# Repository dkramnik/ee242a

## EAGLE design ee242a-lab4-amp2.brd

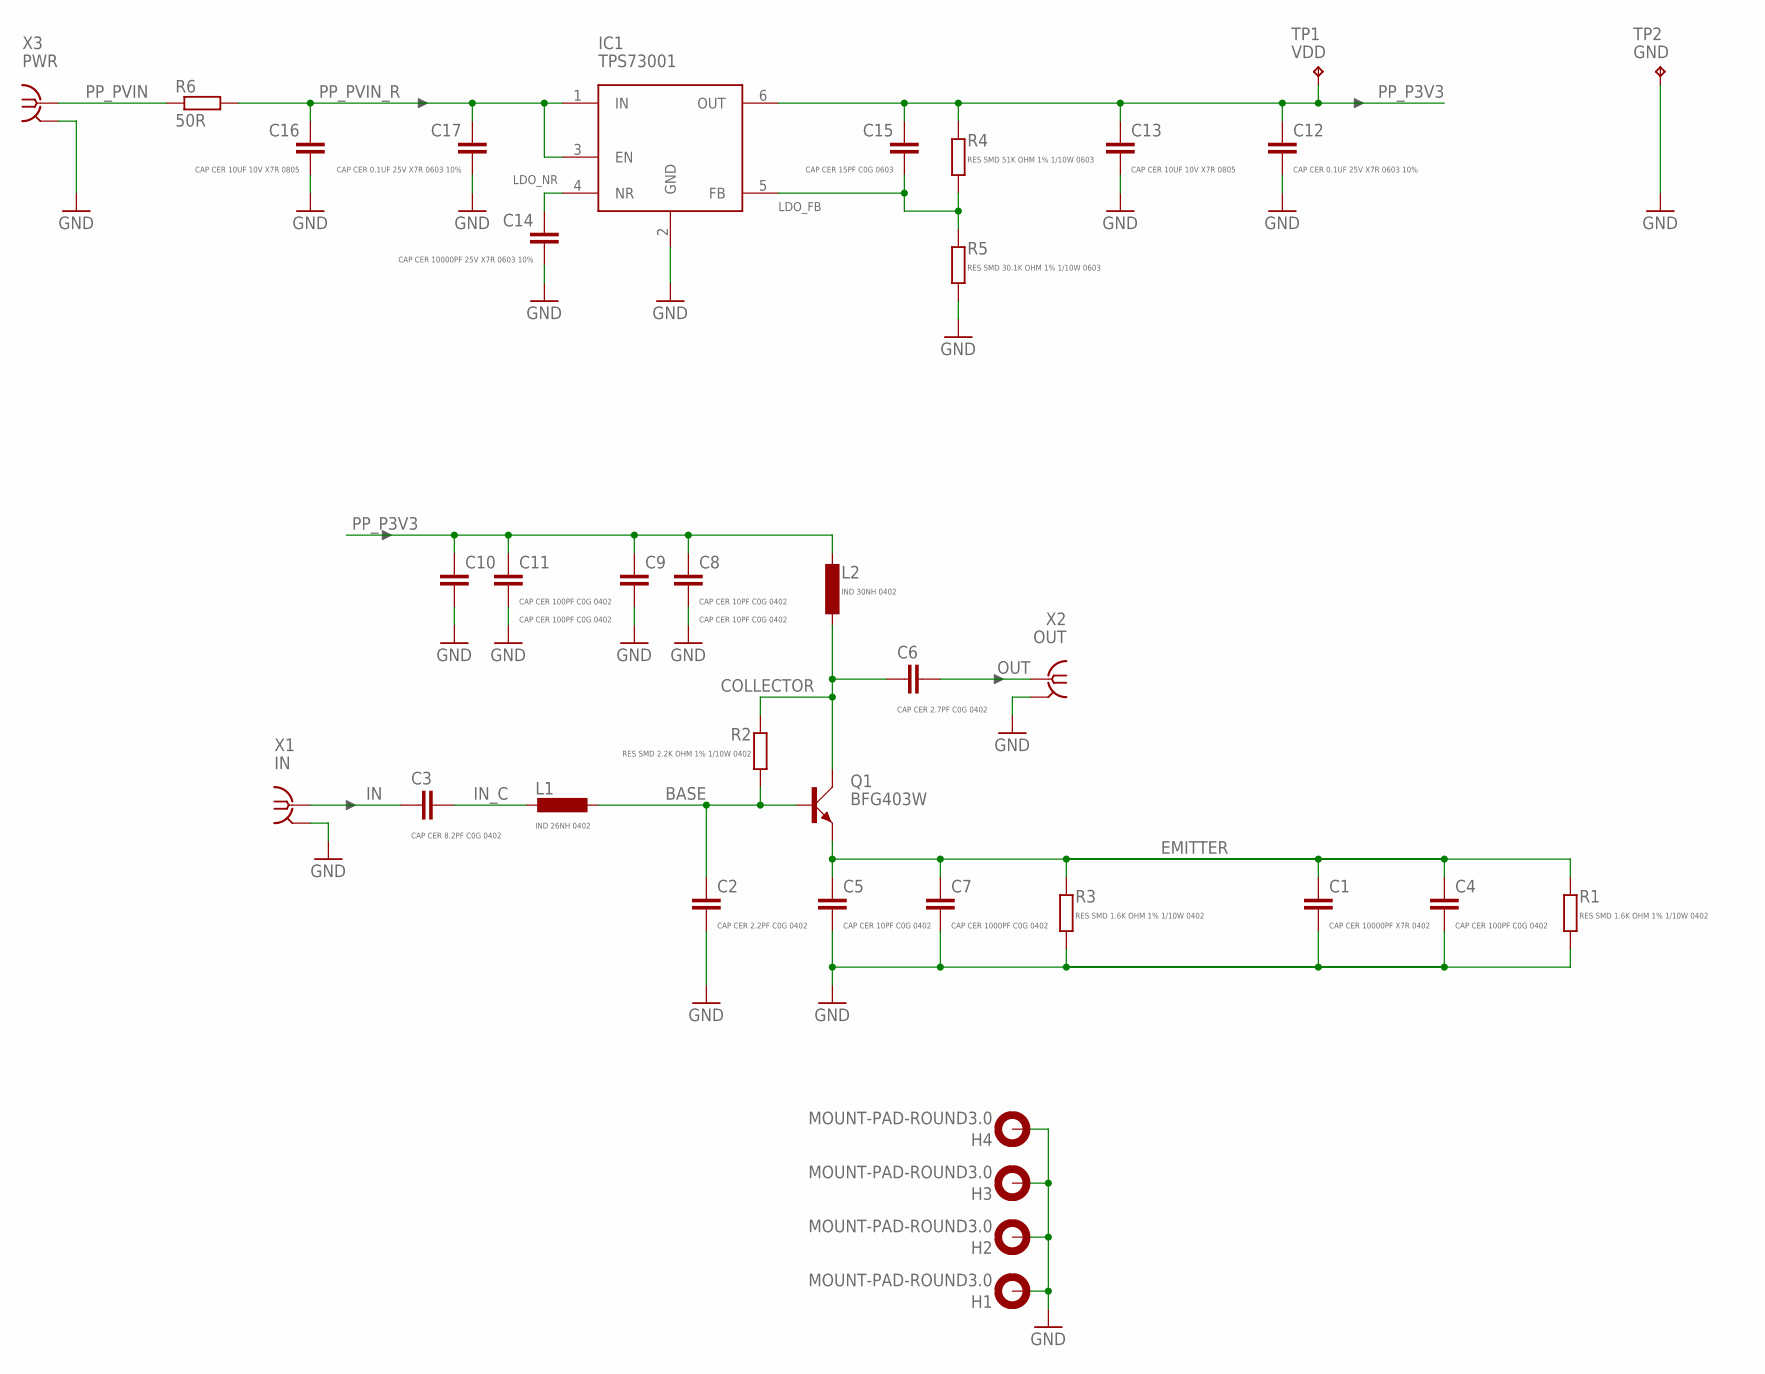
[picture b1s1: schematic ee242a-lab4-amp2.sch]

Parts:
C1: CAP CER 10000PF X7R 0402; C0402
C2: CAP CER 2.2PF C0G 0402; C0402
C3: CAP CER 8.2PF C0G 0402; C0402
C4, C10, C11: CAP CER 100PF C0G 0402; C0402
C5, C8, C9: CAP CER 10PF C0G 0402; C0402
C6: CAP CER 2.7PF C0G 0402; C0402
C7: CAP CER 1000PF C0G 0402; C0402
C12, C17: CAP CER 0.1UF 25V X7R 0603 10%; C0603
C13, C16: CAP CER 10UF 10V X7R 0805; C0805
C14: CAP CER 10000PF 25V X7R 0603 10%; C0603
C15: CAP CER 15PF C0G 0603; C0603
H1, H2, H3, H4: MOUNT-PAD-ROUND3.0; 3,0-PAD
IC1: TPS73001; SOT23-6L
L1: IND 26NH 0402; R0402
L2: IND 30NH 0402; R0402
Q1: BFG403W; SOT343R
R1, R3: RES SMD 1.6K OHM 1% 1/10W 0402; R0402
R2: RES SMD 2.2K OHM 1% 1/10W 0402; R0402
R4: RES SMD 51K OHM 1% 1/10W 0603; R0603
R5: RES SMD 30.1K OHM 1% 1/10W 0603; R0603
R6: 50R; R0805
TP1: VDD; KEYSTONE_5000_MINIATURE
TP2: GND; KEYSTONE_5000_MINIATURE
X1: IN; J502-ND-142-0701-881/886
X2: OUT; J502-ND-142-0701-881/886
X3: PWR; J502-ND-142-0701-881/886

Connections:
BASE: C2.1, L1.2, Q1.2 (B), R2.2
COLLECTOR: C6.1, L2.2, Q1.4 (C), R2.1
EMITTER: C1.1, C4.1, C5.1, C7.1, Q1.1 (E), Q1.3 (E), R1.1, R3.1
GND: C1.2, C2.2, C4.2, C5.2, C7.2, C8.2, C9.2, C10.2, C11.2, C12.2, C13.2, C14.2, C16.2, C17.2, H1.B3,0, H2.B3,0, H3.B3,0, H4.B3,0, IC1.2 (GND), R1.2, R3.2, R5.2, TP2.P$1, X1.G@1 (GND), X1.G@2 (GND), X1.G@3 (GND), X1.G@4 (GND), X2.G@1 (GND), X2.G@2 (GND), X2.G@3 (GND), X2.G@4 (GND), X3.G@1 (GND), X3.G@2 (GND), X3.G@3 (GND), X3.G@4 (GND)
IN: C3.1, X1.1
IN_C: C3.2, L1.1
LDO_FB: C15.2, IC1.5 (FB), R4.1, R5.1
LDO_NR: C14.1, IC1.4 (NR)
OUT: C6.2, X2.1
PP_P3V3: C8.1, C9.1, C10.1, C11.1, C12.1, C13.1, C15.1, IC1.6 (OUT), L2.1, R4.2, TP1.P$1
PP_PVIN: R6.1, X3.1
PP_PVIN_R: C16.1, C17.1, IC1.1 (IN), IC1.3 (EN), R6.2

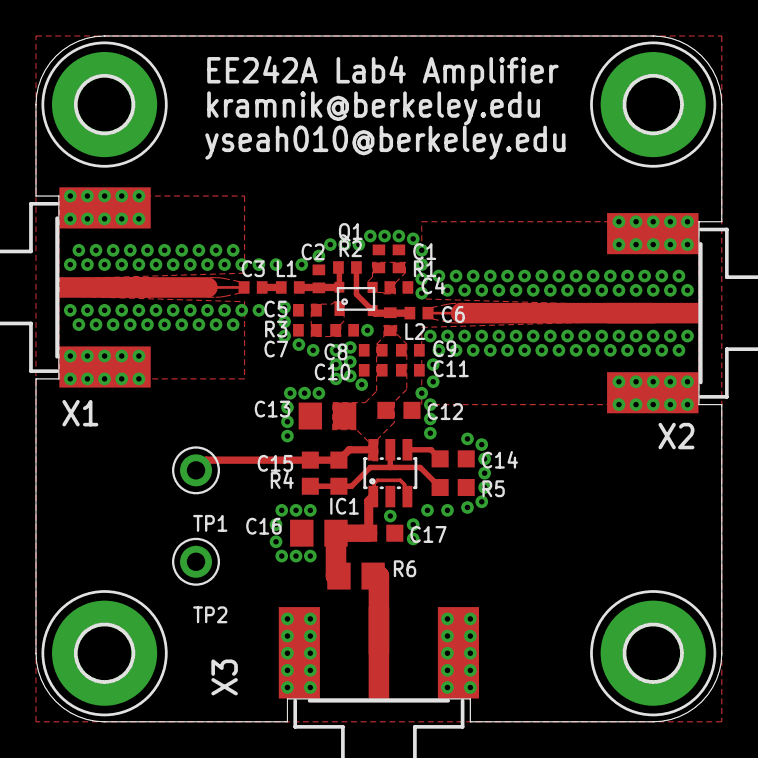
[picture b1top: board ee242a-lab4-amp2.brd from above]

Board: 2 copper layers, 38.1 x 38.1 mm, 36 parts (0 on the bottom side), 12 nets.

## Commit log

2018-11-02 Added standard gitignore for eagle PCBA
2018-11-02 created schematic
2018-11-04 Added libraries
2018-11-06 PCBA sendout 1
2018-11-06 Created and ordered BOM
2018-11-15 Updated component values
2018-12-09 Started oscillator board
2019-01-04 Cleanup
